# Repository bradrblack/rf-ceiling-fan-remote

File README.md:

# rf-ceiling-fan-remote

Voice control for a combo ceiling fan + light, driven by directly cloning the RF remote's signal instead of physically pressing its buttons.

## Background

The original version of this project used a relay module wired across the buttons on the fan's remote control, triggered by an ESP32 listening on an Adafruit IO feed (fed via IFTTT/Google Assistant or iOS Shortcuts). It worked, but relays clicking against physical remote buttons is mechanically unreliable, and Google later removed the IFTTT conversational-actions feature that made flexible voice phrases possible.

This version replaces the relay entirely: a CC1101 RF transceiver connected directly to the ESP32 sniffs the remote's actual RF codes once, and then re-transmits them on command. Voice control goes through [SinricPro](https://sinric.pro), which exposes the fan and light as native devices in Google Home/Assistant (no relay, no fixed IFTTT phrases, natural voice commands like "set the fan to medium").

## Hardware

- ESP32-C3 Super Mini
- CC1101 RF transceiver module (433MHz-marketed hardware; this fan's remote actually operates at 304.25MHz, which the CC1101's synthesizer can still tune to directly)
- The fan's original remote control (used once, to sniff its codes)

## Wiring

| CC1101 pin | ESP32-C3 Super Mini pin |
|---|---|
| VCC | 3V3 (**3.3V only** — do not connect to 5V) |
| GND | GND |
| SCK | GPIO4 |
| MOSI | GPIO6 |
| MISO | GPIO5 |
| CS / SS | GPIO7 |
| GDO0 | GPIO3 |

A 100µF capacitor across the CC1101's VCC/GND pins (as close to the module as possible) was needed to get reliable SPI communication once the module started drawing the higher current TX requires — worth including if you build this yourself.

## Project structure

This is a multi-sketch PlatformIO project — each `.ino`/`.cpp` lives in its own subdirectory under `src/`, with a matching `[env]` in `platformio.ini` that filters the build to just that sketch:

| Environment | Source | Purpose |
|---|---|---|
| `c3_mini` (default) | `src/sniff.ino` | Listens on the CC1101 and prints the decimal code, bit length, protocol number, and pulse length for every button pressed on the physical remote. Run this first to capture your own remote's codes. |
| `c3_mini_tx` | `src/tx_test/` | Standalone transmit test — sends a single code on a timer, used for bench-testing range and signal timing independent of SinricPro/WiFi. |
| `c3_mini_fan` | `src/fan_control/` | The production firmware: connects to WiFi and SinricPro, and re-transmits the correct RF code when a fan or light command comes in. Also supports an optional second fan, independently TR313A or SST12 — see [Fan 2](#fan-2-experimental-second-fanremote) below (**experimental for SST12**). |
| `c3_mini_fan_public` | `src/fan_control_public/` | Same as `c3_mini_fan`, but for sharing with someone else who has the same fan/remote hardware — see [For other users](#for-other-users) below. **TR313A only — no fan2/SST12 support.** |

Build/upload a specific environment with:
```
pio run -e c3_mini_fan -t upload
```

## This fan's captured RF codes

Captured with `sniff.ino` — protocol 11, 12-bit, ~412µs pulse length.

This remote's codes encode two things in the same 12-bit value: which button was pressed, and the remote's 4-position **DIP switch** address (under the battery cover) — so a fan only responds to a remote configured with the same switch positions, and multiple fans can share the same frequency/protocol without answering each other's remote. Sniffing the same 5 buttons across 3 different switch combinations showed the low 4 bits are exactly the DIP address (switch 1 → bit 3 down to switch 4 → bit 0, **OFF = 1, ON = 0**) and the upper 8 bits are the button, unaffected by the switches:

| Button | Base code (all switches ON) |
|---|---|
| Fan low | 2032 |
| Fan medium | 3824 |
| Fan high | 3952 |
| Fan off | 4016 |
| Light toggle | 3056 |

A fan's actual codes are `base | address_nibble`. This fan's remote is set to 1=off, 2=off, 3=on, 4=on (address nibble `1100` = 12), giving 2044/3836/3964/4028/3068 — the codes this project originally shipped with, before the DIP addressing was understood.

The firmware computes the real codes at boot from the base table above plus the configured switch positions (`DIP_SWITCH_1..4` in `secrets.h`, or the portal fields for `c3_mini_fan_public`) — you don't need to sniff a separate code set per fan, just tell it the switch positions.

If you're cloning this for a different remote, re-run `sniff.ino` with all DIP switches ON to capture a fresh base table, and update `RF_CODE_*_BASE`/protocol/pulse length in `src/fan_control/fan_control.cpp` (and `fan_control_public.cpp`).

## Setup

1. **Sniff your remote's codes** — flash `c3_mini`, open a serial monitor, and press each button once. Note the decimal code, protocol number, and pulse length for each.
2. **Create a SinricPro account** at [sinric.pro](https://sinric.pro) and add two devices:
   - A **Fan (US)** device — supports the 3-speed range this fan uses
   - A **Switch** device — for the light toggle
   (Free tier allows up to 3 devices.)
3. **Fill in credentials** — copy `src/fan_control/secrets.h.example` to `src/fan_control/secrets.h` (gitignored) and fill in your WiFi SSID/password, SinricPro App Key/Secret, both device IDs, and your remote's DIP switch positions (`DIP_SWITCH_1..4` — see [This fan's captured RF codes](#this-fans-captured-rf-codes) above).
4. **Flash the production firmware**: `pio run -e c3_mini_fan -t upload`
5. **Link SinricPro to Google Home** from the Google Home app (Works with Google / SinricPro integration) — the fan and light will show up as native devices, controllable by voice with no fixed phrase list.

## For other users

`c3_mini_fan` (above) compiles your WiFi and SinricPro credentials in from `secrets.h`, which is convenient for one device you control but means sharing it with someone else requires them to edit and rebuild the source. `c3_mini_fan_public` (`src/fan_control_public/`) covers the fan 1 (TR313A) side of that same firmware — same CC1101 wiring, same RF codes/watchdogs/reliability behavior — but collects WiFi and SinricPro credentials at first boot through a [WiFiManager](https://github.com/tzapu/WiFiManager) captive portal instead, so someone with the **same fan/remote hardware** can flash it and configure it themselves without touching any code. It does not include `c3_mini_fan`'s [fan 2 support](#fan-2-experimental-second-fanremote) — that stays a `secrets.h`/rebuild-only, experimental feature for now.

This replaces the WiFi/SinricPro *credentials* and the remote's *DIP switch address* with portal fields — the base RF codes, CC1101 pins, and RF frequency/protocol are still compile-time constants in the source, since those are specific to this exact fan/remote model. It's for sharing the same physical build (same remote model, possibly a different individual fan/DIP address), not a general-purpose RF-cloning tool.

Setup, for the person flashing it:

1. **Flash it**: `pio run -e c3_mini_fan_public -t upload` (no `secrets.h` needed for this target).
2. **Connect to the setup network** — on first boot (or whenever it can't connect to a previously saved WiFi network), it opens a WiFi access point named `FanControllerSetup`. Connect to it from a phone or laptop.
3. **Fill in the portal** — a captive portal page should open automatically (or navigate to `192.168.4.1`); choose your home WiFi network and enter its password, plus your own SinricPro App Key, App Secret, Fan device ID, and Light device ID (from your own SinricPro account — see [Setup](#setup) above for creating those devices), your remote's 4 DIP switch positions (`on`/`off` each, matching the physical sliders under the battery cover), and optionally a device hostname (defaults to `myfan`, see below).
4. Submit — the device saves those to flash, computes its RF codes from the DIP positions, connects to your WiFi, and starts talking to SinricPro. If it ever fails to connect (e.g. moved to a new network), it automatically reopens the `FanControllerSetup` portal (DIP/SinricPro fields stay saved).

Unlike `c3_mini_fan`, this build has no ntfy.sh push notifications — reboot reasons are still logged to serial for anyone debugging, just not pushed anywhere, to keep the shared build simpler and dependency-free for other users.

### Hostname, mDNS, and OTA updates

The device is reachable on the local network at `http://<hostname>.local` (default hostname `myfan`, changeable in the setup portal). This is used for:

- **OTA flashing during development**: `pio run -e c3_mini_fan_public -t upload --upload-port myfan.local` flashes over WiFi instead of USB.
- **Firmware updates without a cable, for anyone**: hold the **BOOT button** (GPIO9 on most ESP32-C3 boards) for 10 seconds to wipe the saved WiFi/SinricPro config and reboot into the `FanControllerSetup` portal — then, instead of (or in addition to) reconfiguring WiFi, use the portal's built-in **Update** page to upload a `.bin` firmware file directly from a browser. This is a stock WiFiManager feature, not custom code. Note the setup AP is open/unauthenticated by default, so this window is only as secure as who can join your WiFi during the brief time it's active.

### Multiple fan units

The remote's DIP switches address multiple physically distinct fans on the same frequency/protocol — each fan only responds to a remote (or this controller) configured with its matching switch positions. If you have more than one of these controllers on the same network, give each a distinct hostname in the setup portal (`myfan`, `myfan2`, etc.) *and* set its own DIP fields to match the specific fan it's paired with.

## Fan 2 (experimental, second fan/remote)

`fan_control.cpp` can optionally drive a second physical fan alongside the first, each independently choosing its remote family via `FAN1_REMOTE_TYPE`/`FAN2_REMOTE_TYPE` in `secrets.h`:

- **`REMOTE_TR313A`** (fan 1's default) — same DIP-switch-addressed code family described above, just a different DIP address for the second fan.
- **`REMOTE_SST12`** (fan 2's default) — a different remote chip (used by some NOMA fans) that pairs directly to the fan's receiver instead of using DIP switches. It has no combined low/medium/high scheme — a dedicated button per speed (1-6) plus separate Off and Light-toggle buttons — and every button's code is unique to that one paired remote/receiver, with no derivable address formula the way TR313A has.

**This only works today if you already own a remote that's paired to the fan** — you sniff its buttons with `sniff.ino` (see `secrets.h.example` for the exact `FANn_RF_CODE_*` fields) and this firmware then impersonates that already-paired remote. There is no support for *pairing a new remote from scratch* (provisioning a bare receiver that has no working remote) — SST12 pairing is receiver-side (a power-cycle-then-button-combo handshake within a few seconds), and reproducing it would require reverse-engineering what a genuine remote actually transmits during that handshake, which hasn't been done. If you don't already have a paired, working remote for the fan you want to add, this won't help you.

Fan 2's fan and light SinricPro devices (`FAN2_ID`/`LIGHT2_ID`) are each independently optional, so a build can be fan-only, light-only, both, or neither, to fit within SinricPro's free 3-device tier or not.

Given the pairing gap above, this is closer to "works for one specific home's specific hardware" than a general-purpose feature — there's no `c3_mini_fan_public`-equivalent shareable build for fan 2 yet.

## Known limitation

The remote only has a single **light toggle** button, not separate on/off codes. The firmware tracks an assumed light state locally and only fires the toggle when a voice command's requested state differs from that tracked state. If the light is ever toggled some other way (the original remote, a wall switch), the tracked state can drift out of sync with reality — there's no feedback path from the fan to detect this.

## Reliability

The production firmware (`fan_control.cpp`) includes a few self-healing measures for a device meant to run unattended indefinitely:

- **Bounded WiFi connect at boot** — if WiFi doesn't connect within 30s, it reboots and retries, instead of hanging forever.
- **WiFi watchdog** — if WiFi drops and stays disconnected for 60s during normal operation, it reboots.
- **SinricPro watchdog** — WiFi staying connected doesn't guarantee SinricPro's WebSocket/TLS connection is actually up. Tracks time since the last successful SinricPro connection independently of WiFi state, and reboots if it's been unreachable for 10 minutes — added after a field log showed WiFi stay associated for over an hour while SinricPro was unreachable (DNS/TLS failures), invisible to the WiFi watchdog, recovering only because SinricPro's own internal retry logic eventually got lucky.
- **Radio watchdog** — every 60s, re-checks that the CC1101 still answers over SPI (the same VERSION-register check done at boot). Catches the radio silently wedging mid-operation — a failure mode where WiFi/SinricPro stay connected (Google Assistant still gives its ack "beep") but the RF commands stop actually transmitting. Fixes itself with a reboot rather than needing a manual power cycle.
- **Daily scheduled reboot** — once a day at 3am (`REBOOT_HOUR`, US Eastern via the `TZ_STRING` POSIX timezone string, DST-aware), it reboots proactively to guard against slow heap fragmentation from the long-running SinricPro WebSocket/TLS connection. Time is synced via NTP at boot.
- **Unexpected reset detection** — a crash, a hung SSL/network stack triggering the hardware watchdog, a brownout, etc. bypass the above watchdogs entirely, since they reset the chip before any of our own code gets to run. On the next boot, `esp_reset_reason()` is checked against the reset that just happened; if it wasn't a normal power cycle/reset button press or one of our own deliberate `ESP.restart()` calls, it's reported the same way the other reboots are, instead of leaving an unexplained gap.

If you're deploying this outside US Eastern, update `TZ_STRING` in `fan_control.cpp` to your own [POSIX TZ string](https://developer.ibm.com/articles/au-aix-posix/).

### Reboot notifications

Since these self-healing reboots would otherwise happen silently, the reason for each one is written to flash (NVS) right before restarting, then read back and pushed as a [ntfy.sh](https://ntfy.sh) notification once WiFi reconnects on the next boot — so a device that's rebooting every 10 minutes shows up as a stream of pushes on your phone instead of going unnoticed. A normal manual power cycle leaves no reason behind, so it stays quiet.

To enable it: pick a random, unguessable topic name (ntfy topics are unauthenticated — anyone who knows the exact name can read the notifications), set it as `NTFY_TOPIC` in `secrets.h`, and subscribe to that same topic in the [ntfy app](https://ntfy.sh/app) (iOS/Android) or web app.

### Acknowledgements

Thanks to Chris Butler for 3D printing the first case prototype!

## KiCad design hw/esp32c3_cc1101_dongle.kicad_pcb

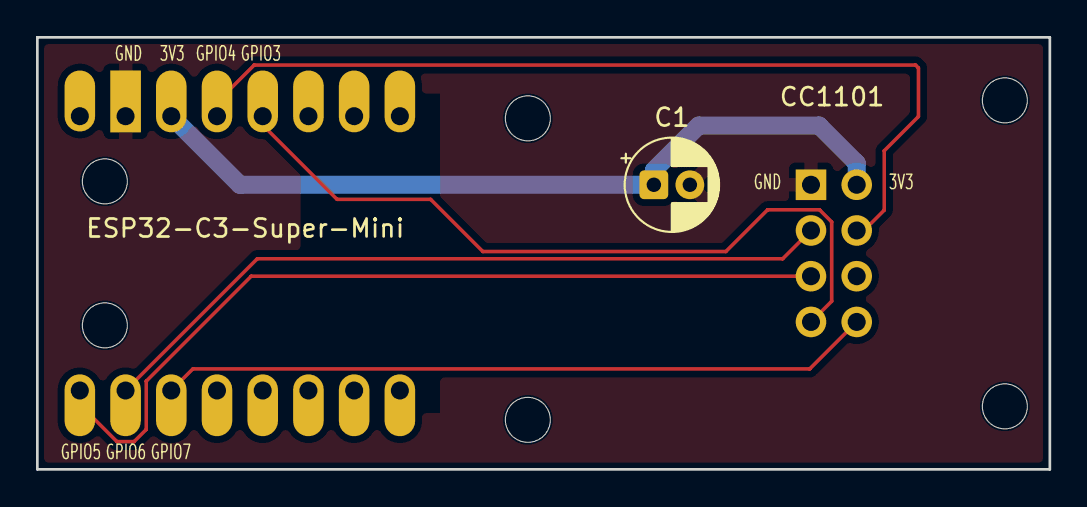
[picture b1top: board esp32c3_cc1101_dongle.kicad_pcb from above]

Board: 2 copper layers, 56.2 x 24.0 mm, 3 parts (0 on the bottom side), 7 nets.

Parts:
C1: 100uF; CP_Radial_D5.0mm_P2.00mm
CC1101: CC1101_Module; CC1101_2x4_Socket
ESP32-C3-Super-Mini: ESP32-C3_SuperMini; ESP32-C3_SuperMini_FaceUp

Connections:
3V3: C1.1, CC1101.5, ESP32-C3-Super-Mini.3
CC1101_GDO0: CC1101.4, ESP32-C3-Super-Mini.5
GND: C1.2, CC1101.1, ESP32-C3-Super-Mini.2
SPI_CSN: CC1101.8, ESP32-C3-Super-Mini.11
SPI_MISO: CC1101.3, ESP32-C3-Super-Mini.9
SPI_MOSI: CC1101.2, ESP32-C3-Super-Mini.10
SPI_SCK: CC1101.6, ESP32-C3-Super-Mini.4

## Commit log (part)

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2024-07-06 added files
2024-07-06 updated src file
